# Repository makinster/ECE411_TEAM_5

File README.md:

# ECE411 Team 5
Team 5 Project - Shooting Chronograph
Members: Sean Schorzman, Kelly Makinster, Jaeyoon Lee, Jianyu Hao

https://drive.google.com/drive/u/1/folders/1vWiaBcHWNWfePrjI9KzBYRflg-hPmRDC

**************************************************************************************

   Practicum project - Ballistic Chronograph
   
   ECE 411
   Fall 2019
   
   Team 5: Sean Schorzman, Jaeyoon Lee, Jianyu Hao, Kelly Makinster
                                                                                     
   Description: Displays the speed in fps of an object that passes through a
                set of IR detector sensors. IR sensors are arranged in a PVC
                pipe 8 inches apart with an IR light directily accross from
                each sensor. Upon passing sensor 1, a timer begins and waits
                until either sensor 2 detects an object or a timeout occurs.
                An additional push button input is used to reset IR detector
                light levels in order to adjust detection sensitivity.
                                                                                  
                                                                                  
 **************************************************************************************

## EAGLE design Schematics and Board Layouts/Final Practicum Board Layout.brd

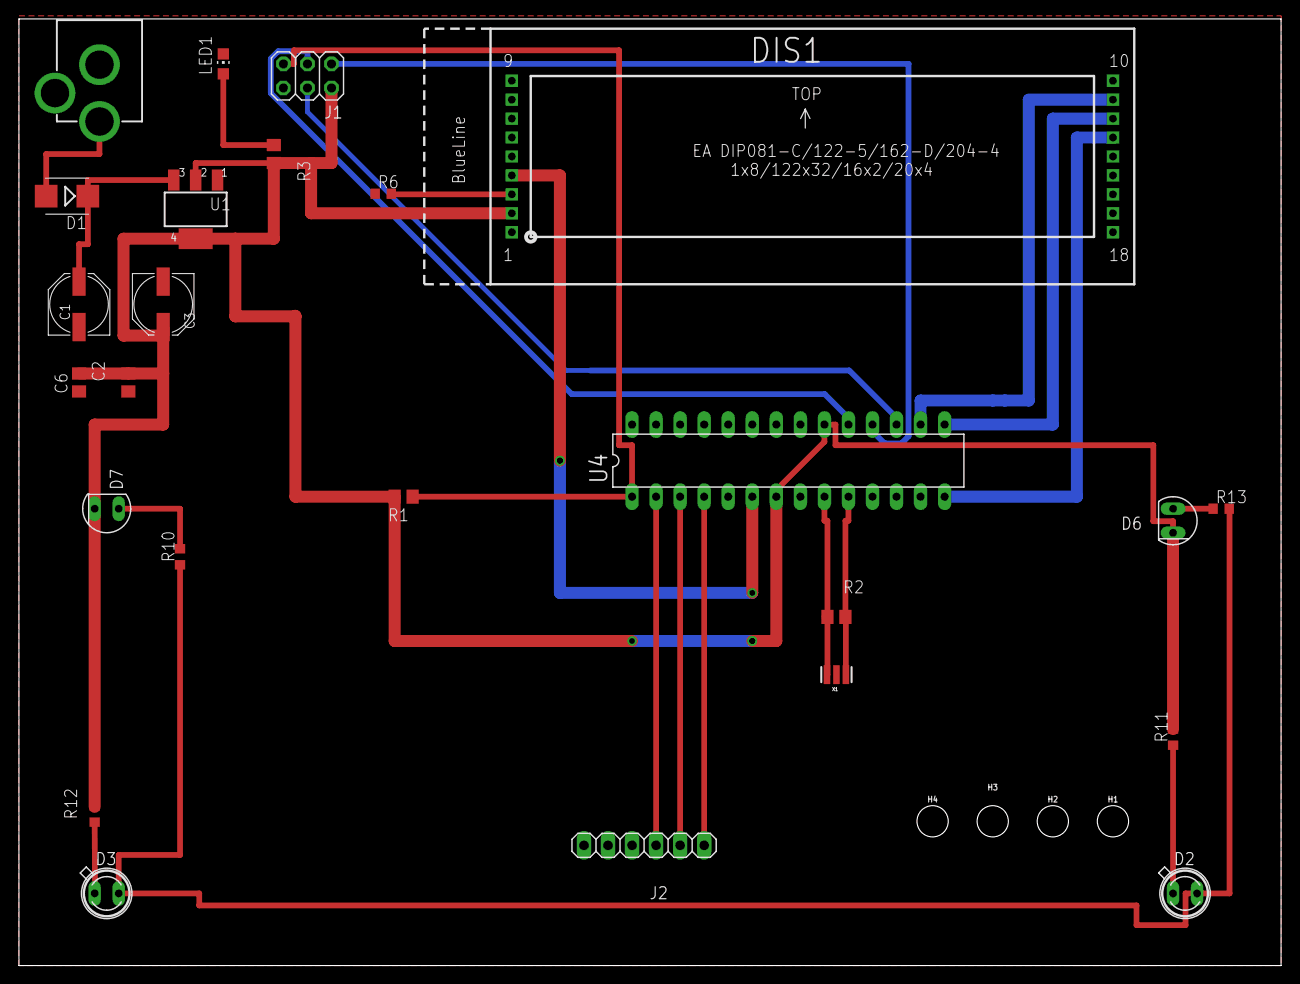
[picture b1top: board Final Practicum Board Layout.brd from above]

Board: 2 copper layers, 133.3 x 100.0 mm, 29 parts (0 on the bottom side), 24 nets.

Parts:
C1, C3: 47u; PANASONIC_D
C2, C6: 100n; C0805
D1: M7; SMB
D2, D3: SFH482
D6, D7: SFH206
DIS1: EA_DIP
H1, H2, H3, H4: STAND-OFF
J1: 3x2 M; 2X03
J2: 1X06
J4: POWER_JACK; POWER_JACK_PTH
LED1: GREEN; CHIP-LED0805
R1: 10K; R0805
R2: 1M; R0805
R3: 1K; R0805
R6: 1K; R0603
R10: 10K; R0603
R11, R12: 100; R0603
R13: 10k; R0603
U1: NCP1117ST50T3G; SOT223
U4: ATMEGA328P-PU; DIL28-3
X1: CSTCE16M0V53-R0 16MHZ; RESONATOR

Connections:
0: D2.K, D3.K, R10.1, R13.2
+5V: C2.2, C3.+, C6.2, D6.K, D7.K, DIS1.2, J1.2, R1.2, R3.2, R11.2, R12.2, U1.2, U1.4, U4.7, U4.20
GND: C1.-, C2.1, C3.-, C6.1, DIS1.1, DIS1.5, DIS1.18, J1.6, J2.6, J4.GND, J4.GNDBREAK, LED1.C, R6.1, U1.1, U4.8, U4.22, X1.2
IR_PAIR1: D6.A, R13.1
IR_PAIR2: D7.A, R10.2
MISO: J1.1, U4.18
MOSI: J1.4, U4.17
unnamed: DIS1.4, U4.6
unnamed: DIS1.3, R6.2
unnamed: LED1.A, R3.1
unnamed: J2.3, U4.2
unnamed: DIS1.13, U4.14
unnamed: DIS1.12, U4.15
unnamed: DIS1.11, U4.16
unnamed: D2.A, R11.1
unnamed: J2.2, U4.3
unnamed: J2.1, U4.4
unnamed: D3.A, R12.1
PWRIN: D1.A, J4.PWR
RESET: J1.5, R1.1, U4.1
SCK: J1.3, U4.19
VIN: C1.+, D1.C, U1.3
XTAL1: R2.1, U4.9, X1.3
XTAL2: R2.2, U4.10, X1.1

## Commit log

2019-10-16 Create Homework 2
2019-10-16 Create empty
2019-10-19 Create Practicum Ideas
2019-10-19 Update Practicum Ideas
2019-11-10 Create Code
2019-11-11 Update Code
2019-11-14 Add files via upload
    https://diagrams.visual-paradigm.com/#proj=0&type=BlockDiagram
    Go to this website and open this file.
2019-11-14 Create Homework #7
2019-12-11 Final Version
    Added file for final version
2019-12-11 Create High Quality Chronograph Test
2019-12-11 Chronograph Final
2019-12-11 Add files via upload
    Bootloader Programming via Arduino Uno Setup
2019-12-11 Added level 0 and level 1 block diagrams
2019-12-11 design log block diagrams
    added block diagrams to design log
2019-12-12 Update High Quality Chronograph Test

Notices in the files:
parts and their libraries:
SparkFun-Hardware: Licensing: Creative Commons ShareAlike 4.0 International - https://creativecommons.org/licenses/by-sa/4.0
